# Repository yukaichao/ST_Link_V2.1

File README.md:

# ST_Link_V2.1

  一个更小的ST_Link V2.1

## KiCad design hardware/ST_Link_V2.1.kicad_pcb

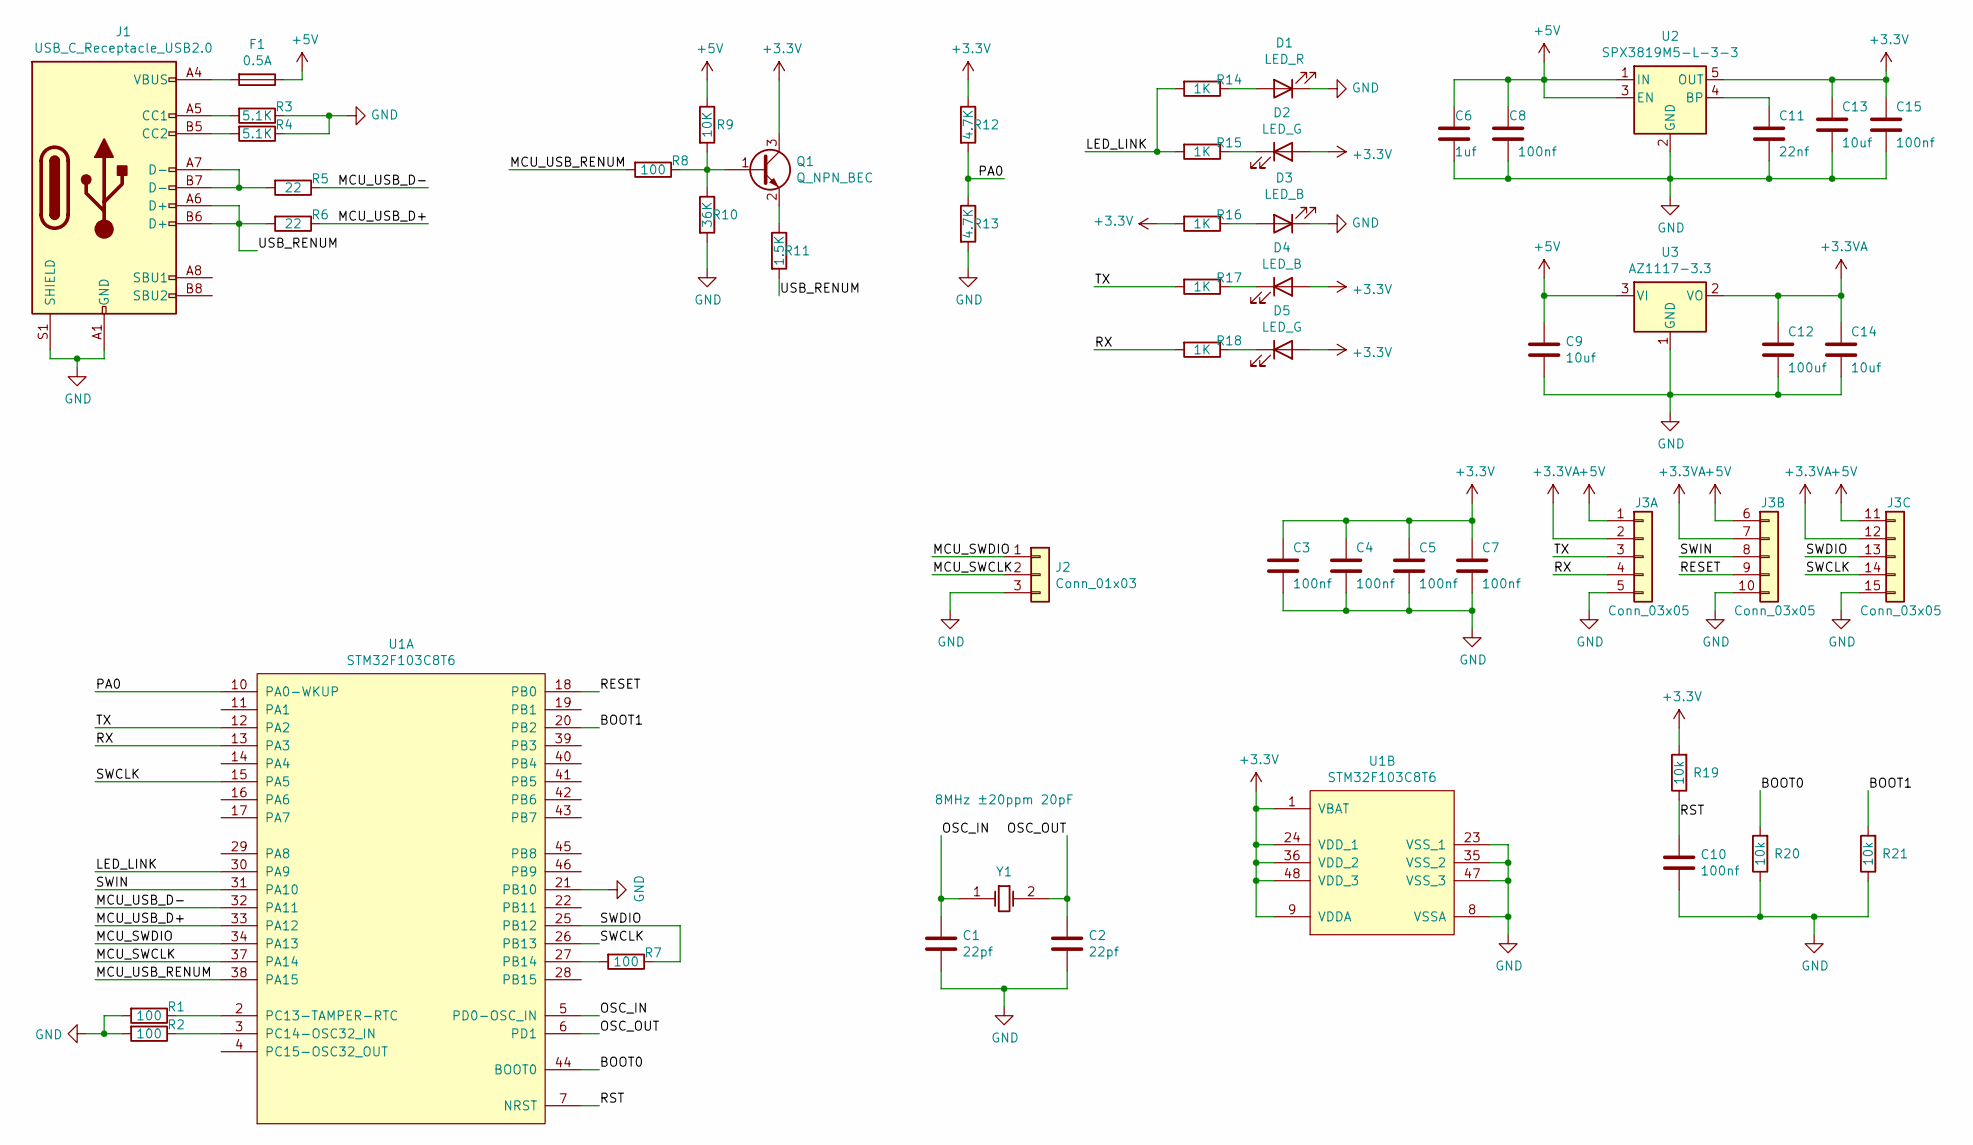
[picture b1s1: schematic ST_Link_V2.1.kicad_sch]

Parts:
C1, C2: 22pf; C_0402_1005Metric
C3, C4, C5, C7, C8, C10, C15: 100nf; C_0402_1005Metric
C6: 1uf; C_0805_2012Metric
C9, C13, C14: 10uf; C_0402_1005Metric
C11: 22nf; C_0402_1005Metric
C12: 100uf; C_1206_3216Metric
D1: LED_R
D2, D5: LED_G
D3, D4: LED_B
F1: 0.5A; Fuse_0805_2012Metric
J1: USB_C_Receptacle_USB2.0; USB_C_Receptacle_Palconn_UTC16-G
J2: Conn_01x03; PinHeader_1x03_P2.54mm_Vertical
J3: Conn_03x05; PinHeader_3x05_P2.54mm_Horizontal
Q1: Q_NPN_BEC; SOT-23
R1, R2, R7, R8: 100; R_0402_1005Metric
R3, R4: 5.1K; R_0402_1005Metric
R5, R6: 22; R_0402_1005Metric
R9: 10K; R_0402_1005Metric
R10: 36K; R_0402_1005Metric
R11: 1.5K; R_0402_1005Metric
R12, R13: 4.7K; R_0402_1005Metric
R14, R15, R16, R17, R18: 1K; R_0402_1005Metric
R19, R20, R21: 10k; R_0402_1005Metric
U1: STM32F103C8T6; LQFP-48_7X7X05P
U2: SPX3819M5-L-3-3; SOT-23-5
U3: AZ1117-3.3; SOT-223
Y1: SMD-5032_2P_8MHz_20ppm_20pF; SMD-5032_2P

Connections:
+3.3VA: C12.1, C14.1, J3.2, J3.7, J3.12, U3.2 (VO)
+3V3: C3.1, C4.1, C5.1, C7.1, C13.1, C15.1, D2.2 (A), D4.2 (A), D5.2 (A), Q1.3 (C), R12.1, R16.2, R19.2, U1.1 (VBAT), U1.9 (VDDA), U1.24 (VDD_1), U1.36 (VDD_2), U1.48 (VDD_3), U2.5 (OUT)
+5V: C6.1, C8.1, C9.1, F1.1, J3.1, J3.6, J3.11, R9.1, U2.1 (IN), U2.3 (EN), U3.3 (VI)
/BOOT0: R20.2, U1.44 (BOOT0)
/BOOT1: R21.2, U1.20 (PB2)
/LED_LINK: R14.2, R15.2, U1.30 (PA9)
/MCU_SWCLK: J2.2, U1.37 (PA14)
/MCU_SWDIO: J2.1, U1.34 (PA13)
/MCU_USB_D+: R6.1, U1.33 (PA12)
/MCU_USB_D-: R5.1, U1.32 (PA11)
/MCU_USB_RENUM: R8.2, U1.38 (PA15)
/OSC_IN: C1.1, U1.5 (PD0-OSC_IN), Y1.1 (OSC1)
/OSC_OUT: C2.1, U1.6 (PD1), Y1.2 (OSC2)
/PA0: R12.2, R13.1, U1.10 (PA0-WKUP)
/RESET: J3.9, U1.18 (PB0)
/RST: C10.1, R19.1, U1.7 (NRST)
/RX: J3.4, R18.2, U1.13 (PA3)
/SWCLK: J3.14, U1.15 (PA5), U1.26 (PB13)
/SWDIO: J3.13, R7.1, U1.25 (PB12)
/SWIN: J3.8, U1.31 (PA10)
/TX: J3.3, R17.2, U1.12 (PA2)
/USB_RENUM: J1.A6 (D+), J1.B6 (D+), R6.2, R11.2
GND: C1.2, C2.2, C3.2, C4.2, C5.2, C6.2, C7.2, C8.2, C9.2, C10.2, C11.2, C12.2, C13.2, C14.2, C15.2, D1.1 (K), D3.1 (K), J1.A1 (GND), J1.A12 (GND), J1.B1 (GND), J1.B12 (GND), J1.S1 (SHIELD), J2.3, J3.5, J3.10, J3.15, R1.2, R2.2, R3.1, R4.1, R10.2, R13.2, R20.1, R21.1, U1.8 (VSSA), U1.21 (PB10), U1.23 (VSS_1), U1.35 (VSS_2), U1.47 (VSS_3), U2.2 (GND), U3.1 (GND)
unnamed: C11.1, U2.4 (BP)
unnamed: D1.2 (A), R14.1
unnamed: D2.1 (K), R15.1
unnamed: D3.2 (A), R16.1
unnamed: D4.1 (K), R17.1
unnamed: D5.1 (K), R18.1
unnamed: F1.2, J1.A4 (VBUS), J1.A9 (VBUS), J1.B4 (VBUS), J1.B9 (VBUS)
unnamed: J1.A5 (CC1), R3.2
unnamed: J1.A7 (D-), J1.B7 (D-), R5.2
unnamed: J1.B5 (CC2), R4.2
unnamed: Q1.1 (B), R8.1, R9.2, R10.1
unnamed: Q1.2 (E), R11.1
unnamed: R1.1, U1.2 (PC13-TAMPER-RTC)
unnamed: R2.1, U1.3 (PC14-OSC32_IN)
unnamed: R7.2, U1.27 (PB14)

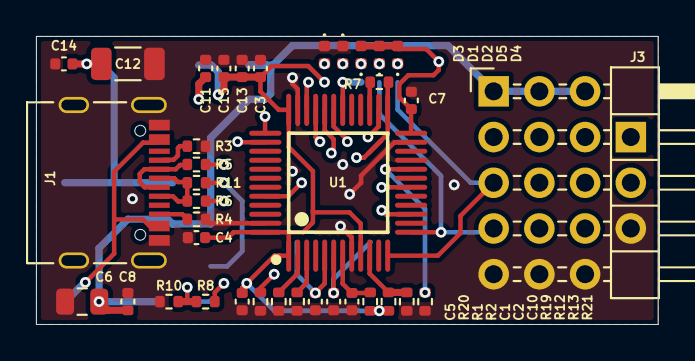
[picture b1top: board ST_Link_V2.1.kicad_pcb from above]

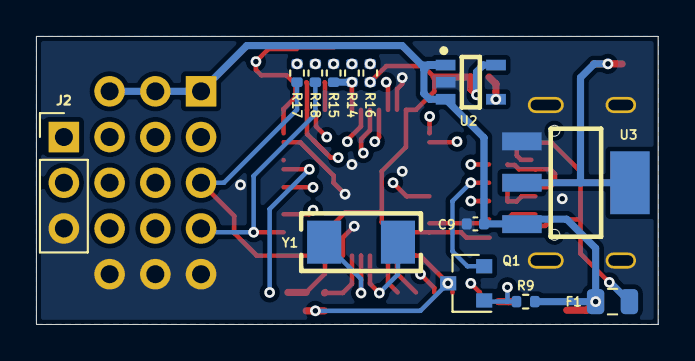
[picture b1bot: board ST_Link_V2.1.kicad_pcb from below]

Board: 4 copper layers, 34.5 x 16.0 mm, 50 parts (13 on the bottom side), 38 nets.

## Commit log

2021-07-10 V1.0
2022-04-05 更改bug
